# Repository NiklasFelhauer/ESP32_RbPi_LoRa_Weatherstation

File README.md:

# ESP32_RbPi_LoRa_Weatherstation

hey everyone!

components used: >1xESP32; >1xRaspberry Pi 4 Modell B; >1xBME280 weather sensor; >2xLoRa RFM95 tranceivers

IDE used: Visual Studio Code (Python: Microsoft Python Extension and C: PlatformIO Extension)

What is LoRa? LoRa (Long Range) is a upcoming RF technology that includes features like long range (depends highly on the area, but up to multiple miles) or low power consumption. So perfect for IoT projects like this one here!

description: ESP32 sends weather data (provided by BME280 sensor) via LoRa tranceiver to LoRa tranceiver (=connected to RbPi). Now, here are 2 directions to go: 1) RbPi sends weather data via MQTT network to NodeRed to display the data on a NodeRed dashboard OR 2) RbPi stores weather data in InflxDB (timestamps based database) to visualize the data in grafana

programming language used: mainly C (ESP32) and Python (Raspberry Pi) > (1) in NodeRed simple html, css, JAVA and JSON codes

planned updates: >3D-printed weatherstation case (I'll upload .stl data soon) >supply ESP32 with battery/solar-charger/solar-panel

more details in the specific folders.

stay tuned! :)

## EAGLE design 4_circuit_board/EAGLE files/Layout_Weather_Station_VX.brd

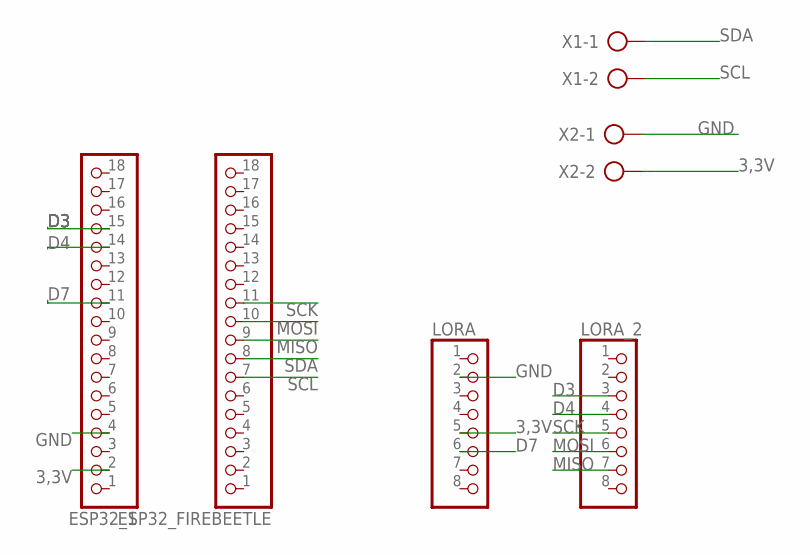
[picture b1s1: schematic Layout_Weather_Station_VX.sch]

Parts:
ESP32_1, ESP32_FIREBEETLE: PINHD-1X18; 1X18
LORA: PINHD-1X8; 1X08
LORA_2: PINHD-1X8; 1X08
X1, X2: AK300/2

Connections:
3,3V: ESP32_1.2, LORA.5, X2.2
D3: ESP32_1.15, LORA_2.3
D4: ESP32_1.14, LORA_2.4
D7: ESP32_1.11, LORA.6
GND: ESP32_1.4, LORA.2, X2.1
MISO: ESP32_FIREBEETLE.9, LORA_2.7
MOSI: ESP32_FIREBEETLE.10, LORA_2.6
SCK: ESP32_FIREBEETLE.11, LORA_2.5
SCL: ESP32_FIREBEETLE.7, X1.2
SDA: ESP32_FIREBEETLE.8, X1.1

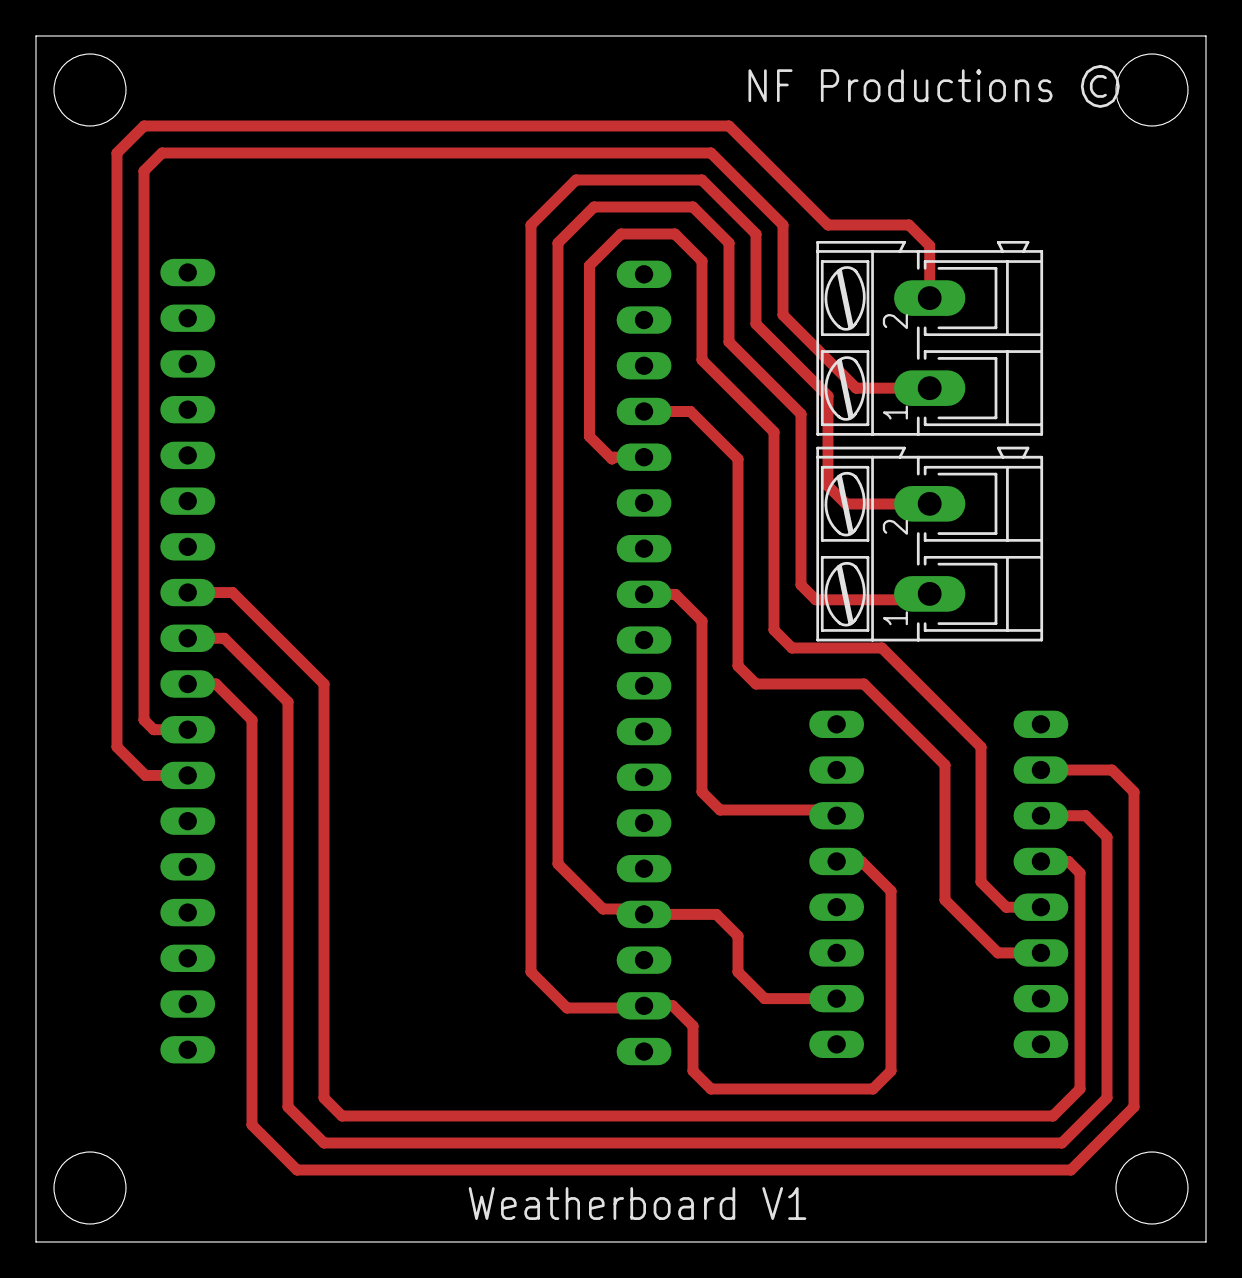
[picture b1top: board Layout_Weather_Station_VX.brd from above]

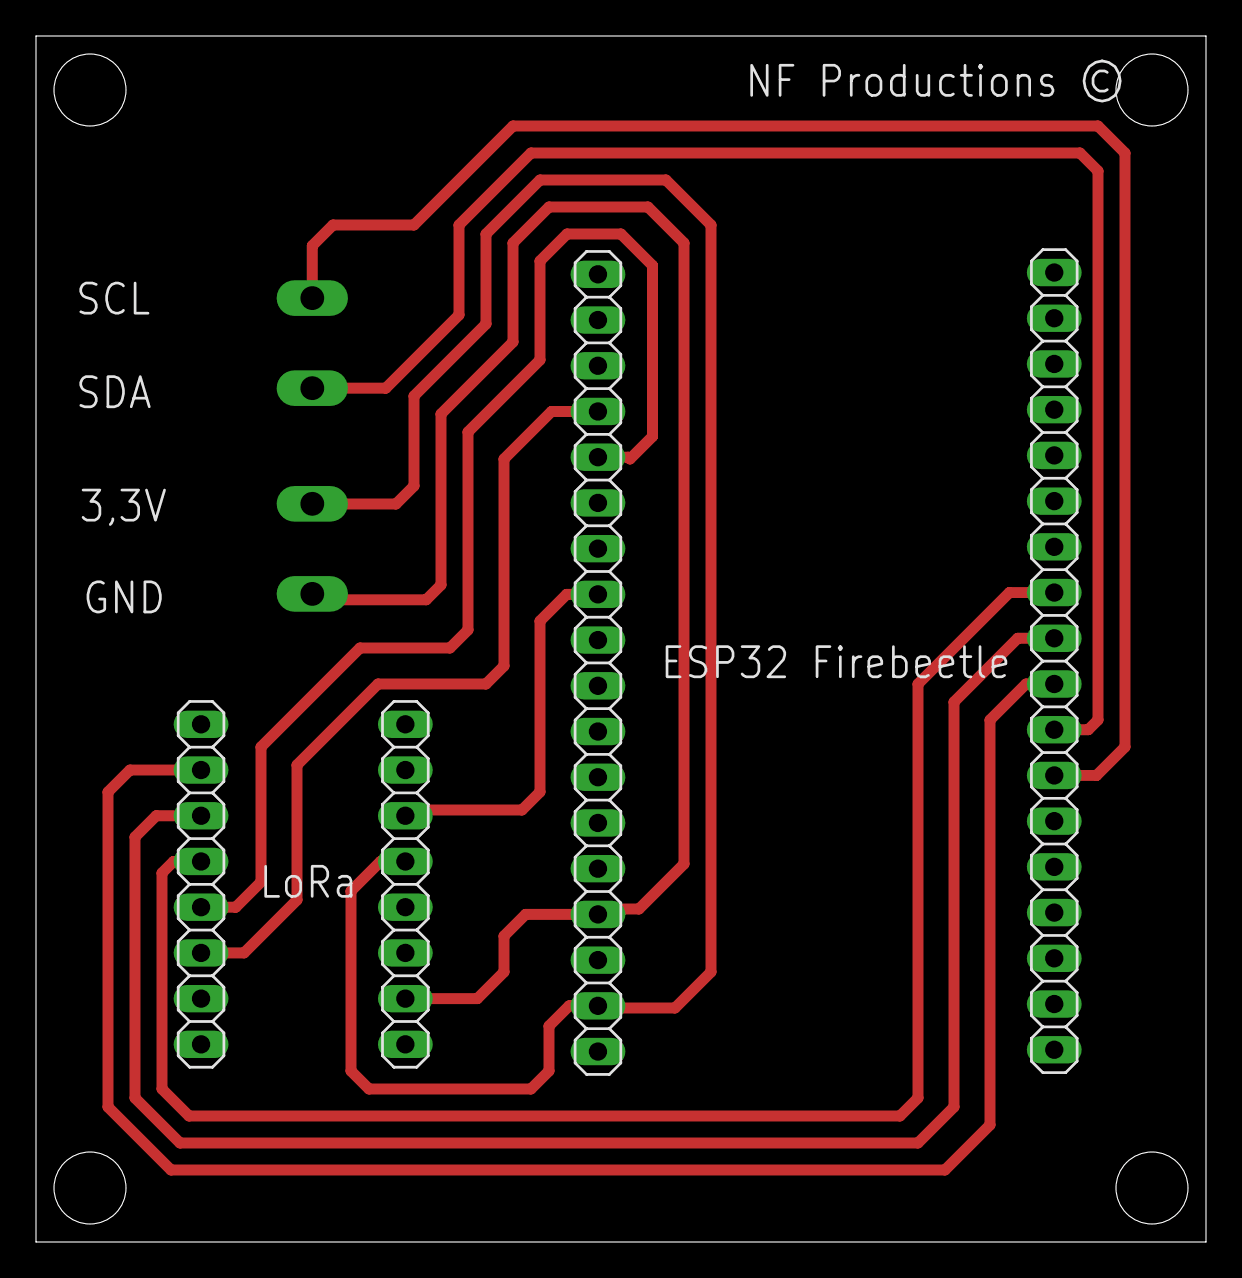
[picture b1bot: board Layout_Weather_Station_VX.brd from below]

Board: 2 copper layers, 65.0 x 67.0 mm, 6 parts (4 on the bottom side), 10 nets.

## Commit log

2020-12-21 Upload ESP32 Code
2020-12-21 Changed data type from .txt to .cpp
2020-12-21 Updated IDE, I used
2020-12-21 Updated NodeRed part with ESP32 LoRa transmitter Code
2020-12-21 Changed some folder names
2020-12-21 Rename raw_code.txt to raw_code.cpp
2020-12-30 Update raw_code.cpp
    Changed to LoRa packet, for bug fixing in python receiver code.
    The setup didn't work for temperatures below 10 °C or F, now it is fixed!
2020-12-30 Update RbPi_LoRa_InfluxDB_grafana.py
    changed the part where payload_data is spiltted in temp, pressure und humidty so it matches the changes in to transmitter file
2021-01-02 added test file, going to remove it again!
2021-01-02 deleted test file
2021-01-02 bug_1: fix for unrealistic measurement peaks (e.g. 4000 °C)
2021-01-02 bug_1.1 filtering unrealistic measurment fails (e.g: 3000 °C)
2021-01-02 bug_1.2 updatet bug_1 so there is a first value for unrealistic meassurement if-loop
2021-01-02 bug_1.2.1 just changed version number in the header
2021-01-02 added some comments
2021-01-02 changed file order
2021-01-02 uploaded BETA python sktipt for RbPi
2021-01-02 Python: NodeRed Code for RbPi updated
2021-01-02 Python: InfluxDB-RbPi: switched logging level from "INFO" to "Warning"
2021-01-03 Upload: LoRa-Communication-Code between to ESP32 NodeMCUs (BETA Version)
2021-01-04 Update: InfluxDB: Python: changed code appearance, outsourced code from main to functions (failFilter and firstValue)
2021-01-13 Update FailFilter
2021-01-13 Changed FailFilter
2021-01-13 FailFilter Update
2021-01-13 FailFilter Range update
2021-01-13 Updated NodeRed Flow example
2021-01-13 changed file names
2021-01-13 updated NodeRed example flow
2021-01-13 NodeRed JSON example flow update
2021-01-22 UPLOAD: most of the casing .stl files.
2021-01-22 UPDATE: new casing parts added
2021-01-23 UPDATE: NodeRed ESP32 raw code
    included delimiter ";" between each LoRa message to split it later on
2021-01-23 UPDATE
    changed temp/humidity/pressure to individual MQTT topics
2021-01-29 UPLOAD: circuit board EAGLE files
